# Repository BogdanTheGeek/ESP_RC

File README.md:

# ESP_RC
An Open-Source Transmitter/Receiver for RC Planes, Cars, Boats and more based on the ESP8266 and ESP32 family of devices

## Operation

The ESP_RC project is based on the functionality of the ESP8266 and ESP32 use p2p comunication though Wi-fi 802.11n without the use of TCP or UDP. This is called ESP-Now and drastically reduces the latency of the transmission enableing real time control of RC vehicles.The two devices are linked together through their MAC address. The receiver sends telemetry to the transmitter and the transmitter sends controls back. The packet size is limited to 250 Bytes.
Current reciever designs are:
smol_boy_V1	
ESP8266 6-CH receiver with Battery voltage monitoring and I2C peripherals for more telemetry

There are no designs yet for a transmitter however there is a Linux Project that allows Direct comunication through ESP-Now from a PC. This might come in handy:
https://github.com/thomasfla/Linux-ESPNOW
The first working transmitter will hopefully be able to use a buetooth controller. From my research, the xbox one s controller is a bit tricky but the PS3 controller has a ESP-IDF library available here:
https://github.com/jvpernis/esp32-ps3
In the future we might want to build a custom controller with maybe even an LCD screen, accelerometer and so on.

## Features 
 - [x] Built in baterry voltage telemetry
 - [x] I2C expansion port telemetry
 - [x] Bluetooth controller support for ESP32
 - [ ] GPS support
 - [ ] Multiple vehicle profiles configurable via AP
 - [ ] Easy vehicle controls setup via AP
 - [ ] Return to home mode (GPS)
 - [ ] Flight-controller features?

## Supported I2C devices
| Support			| Name			| Description													|
|-------------------|---------------|---------------------------------------------------------------|
|:heavy_check_mark:	| BMP280 		| Temp, Altitude, Pressure										|
|:white_check_mark:	| MPU-6050		| Gyro, Acceleremeter											|
|:white_check_mark:	| LSM303D		| Compass, 3D accelerometer and 3D magnetometer module			|
|:white_check_mark:	| MPU-9250		| Gyro, Accelerometer + AK8963 magnetometer						|
|:white_check_mark:	| HMC5883		| Magnetomer													|
|:white_check_mark:	| ITG-3200		| 'Gaming' gyro													|
|:white_check_mark:	| INA219		| Bi-directional current meter									|
|:white_check_mark:	| Wii IR Sensor	| Tracks the 4 brighest IR Points in FOV (Missile tracking?)	|
|:white_check_mark:	| ZOE/SAM-M8Q	| GPS module													|
|:white_check_mark:	| XA1110		| GPS module													|
|:white_check_mark:	| LSM9DS1		| Gyro, Accelerometer, magnetometer								|
|:white_check_mark:	| ADS1115		| 4-CH ADC														|
|:white_check_mark:	| 24LC256		| EEPROM														|

## Credit

WifiEspNow library : https://github.com/yoursunny/WifiEspNow
ESP32-PS3 library : https://github.com/jvpernis/esp32-ps3/tree/develop
Espressif in their holyness.

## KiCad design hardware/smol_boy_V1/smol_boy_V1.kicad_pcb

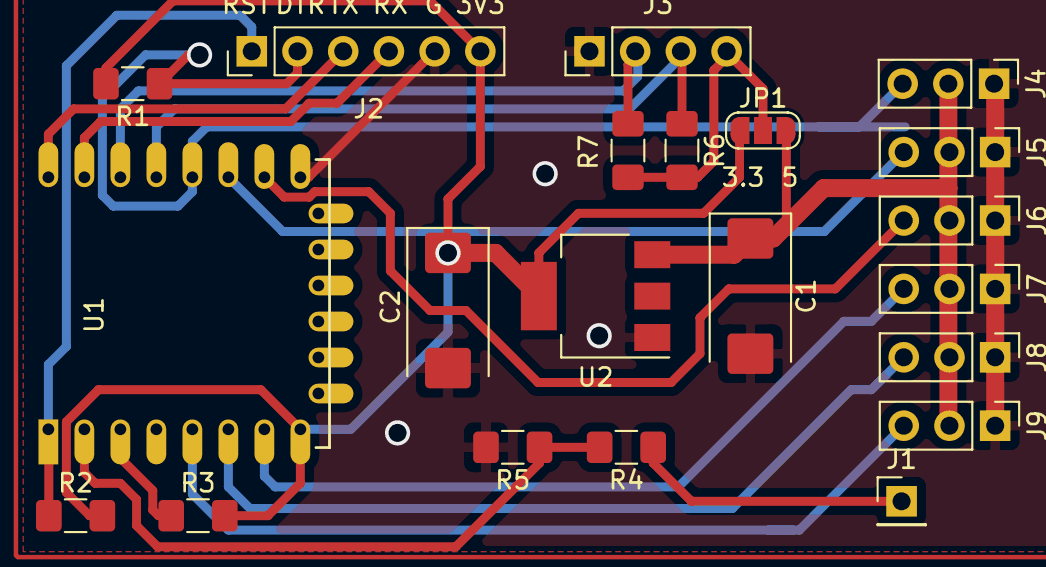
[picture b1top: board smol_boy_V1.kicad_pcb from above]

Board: 2 copper layers, 21 parts (0 on the bottom side), 18 nets.

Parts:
C1, C2: 100uF; CP_EIA-7343-31_Kemet-D_Pad2.25x2.55mm_HandSolder
J1: Conn_01x01_Male; PinHeader_1x01_P2.54mm_Vertical
J2: Conn_01x06_Male; PinHeader_1x06_P2.54mm_Vertical
J3: Conn_01x04_Male; PinHeader_1x04_P2.54mm_Vertical
J4, J5, J6, J7, J8, J9: Conn_01x03_Male; PinHeader_1x03_P2.54mm_Vertical
JP1: Jumper_3_Bridged12; SolderJumper-3_P1.3mm_Open_RoundedPad1.0x1.5mm_NumberLabels
R1, R2, R3, R6, R7: 10k; R_1206_3216Metric_Pad1.42x1.75mm_HandSolder
R4: 100K; R_1206_3216Metric_Pad1.42x1.75mm_HandSolder
R5: 3.3k; R_1206_3216Metric_Pad1.42x1.75mm_HandSolder
U1: ESP-12E
U2: AMS1117-3.3; SOT-223-3_TabPin2

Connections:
+3V3: C2.1, J2.6, JP1.1, R1.2, R2.2, R3.2, U1.8, U2.2
+5V: C1.1, J4.2, J5.2, J6.2, J7.2, J8.2, J9.2, JP1.3, U2.3
ADC: R4.2, R5.1, U1.2
CH0: J2.2, J4.3, R1.1, U1.12
CH1: J5.3, U1.11
CH2: J6.3, U1.10
CH3: J7.3, U1.7
CH4: J8.3, U1.6
CH5: J9.3, U1.5
GND: C1.2, C2.2, J2.5, J3.1, J4.1, J5.1, J6.1, J7.1, J8.1, J9.1, R5.2, U1.9, U2.1
unnamed: J3.4, JP1.2, R6.2, R7.2
unnamed: R3.1, U1.3
RST: J2.1, R2.1, U1.1
RX: J2.4, U1.15
SCL: J3.2, R7.1, U1.14
SDA: J3.3, R6.1, U1.13
TX: J2.3, U1.16
V_BAT: J1.1, R4.1

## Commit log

2019-12-11 work on readme
2019-12-11 fixed previous readme
2019-12-11 layed down the foundation, support for telemetry communinations and different boards
2019-12-11 updated readme for supported i2c devices
2019-12-11 more i2c devices added
2019-12-11 fixed table formatting
2019-12-11 fixed table again formatting
2019-12-11 finally some mf tick boxes in tabels
2019-12-11 extensible initialization of channels
2019-12-11 fixed resistor for v_Bat from 10k to 3.3k as adc range is only 0-1v for 12e module
2019-12-11 adjusted code for new potential divider
2019-12-13 tranmitter implemented
2019-12-13 communication working
2019-12-13 DEBUG compilation option
2019-12-13 debug enabled for tX
2019-12-13 fixed comp errors
2019-12-13 forgot one print statement
2019-12-13 ctrl-s
2019-12-17 fixed pcb channel pins
2019-12-17 removed unnecesery files
2019-12-17 first working communication test
2019-12-17 pcb pullups fixed
2019-12-17 for future use status of message
2019-12-23 PS3 controller input implemented
2019-12-23 NOT TESTED:assigned test channels to ps3 controller
2019-12-26 first working prototype
